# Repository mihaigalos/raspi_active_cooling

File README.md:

# raspi_active_cooling

Repo for cooling things down.

### The Hardware

Essentially a MOSFET driven by a GPIO from the Raspberry Pi, driving the cooling fan.

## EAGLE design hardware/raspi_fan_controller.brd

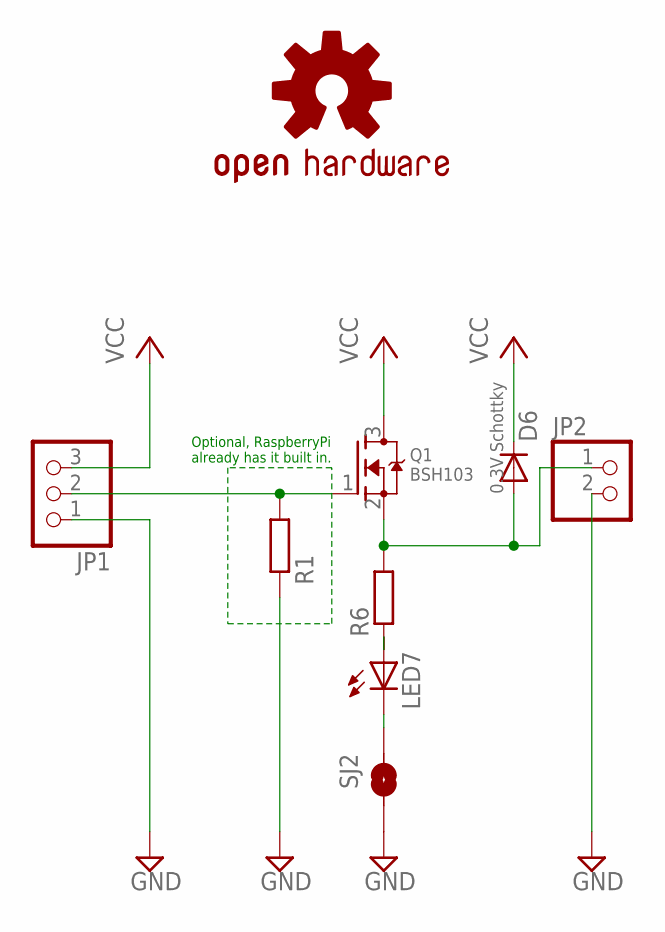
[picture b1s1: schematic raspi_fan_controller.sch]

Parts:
D6: 0.3V Schottky; SOD523
JP1: PINHD-1X3/90; 1X03/90
JP2: PINHD-1X2/90; 1X02/90
LED7: LED0603; LED-0603
LOGO1: OSHW-LOGOS; OSHW-LOGO-S
Q1: BSH103; SOT23
R1, R6: R-EU_R0603; R0603
SJ2: SOLDERJUMPERNO; SJ_2S-NO

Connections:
GND: JP1.1, JP2.2, R1.1, SJ2.2
unnamed: LED7.A, R6.1
unnamed: LED7.C, SJ2.1
unnamed: D6.A, JP2.1, Q1.2 (S), R6.2
TRIGGER: JP1.2, Q1.1 (G), R1.2
VCC: D6.C, JP1.3, Q1.3 (D)

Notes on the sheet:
Optional, RaspberryPi already has it built in.

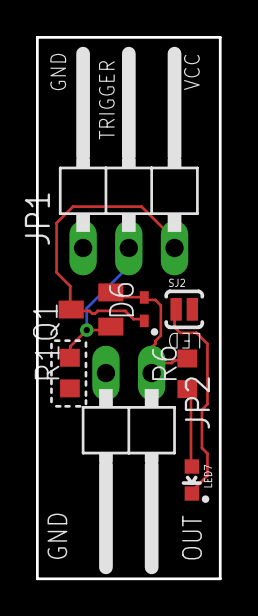
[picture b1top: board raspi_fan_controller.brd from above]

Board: 2 copper layers, 10.2 x 30.1 mm, 9 parts (1 on the bottom side), 6 nets.

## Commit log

2020-11-23 :sunrise: Initial commit
2020-11-23 Improve naming
2020-11-23 Add missing labels for pins and jumper
2020-11-23 Make *.brd gate pulldown optional
2020-11-23 Add dimmensions
2020-11-24 Lfs track *.png
2020-11-24 Update readme with screenshot
2020-11-24 Update png

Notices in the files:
parts and their libraries:
SparkFun-Retired: Licensing: Creative Commons ShareAlike 4.0 International - https://creativecommons.org/licenses/by-sa/4.0
SparkFun: Licensing: CC v3.0 Share-Alike You are welcome to use this library for commercial purposes.
